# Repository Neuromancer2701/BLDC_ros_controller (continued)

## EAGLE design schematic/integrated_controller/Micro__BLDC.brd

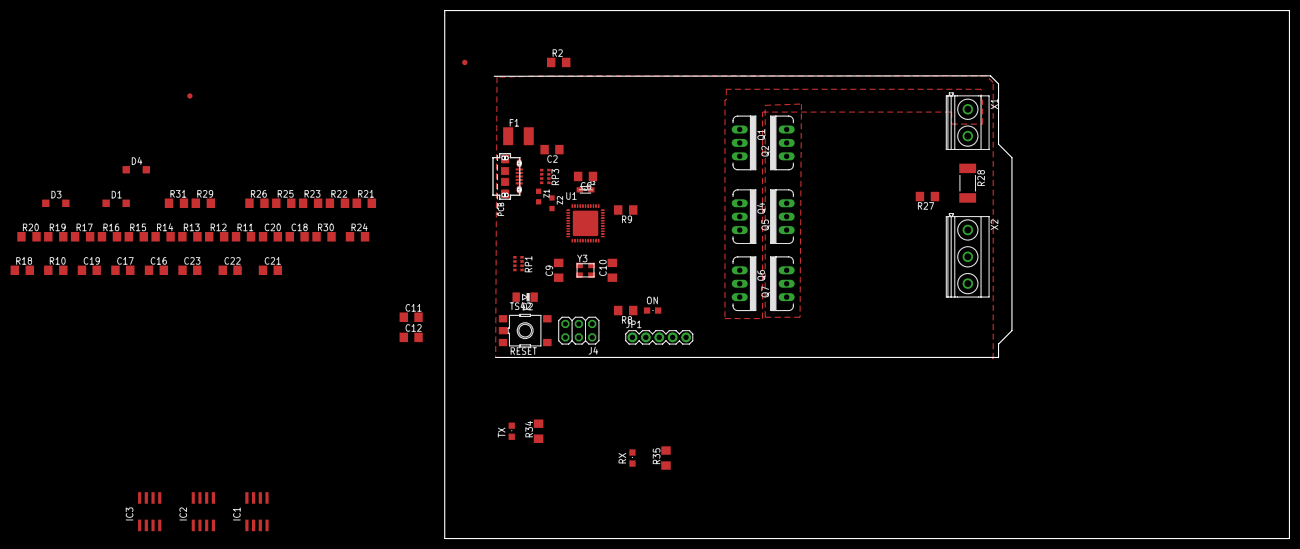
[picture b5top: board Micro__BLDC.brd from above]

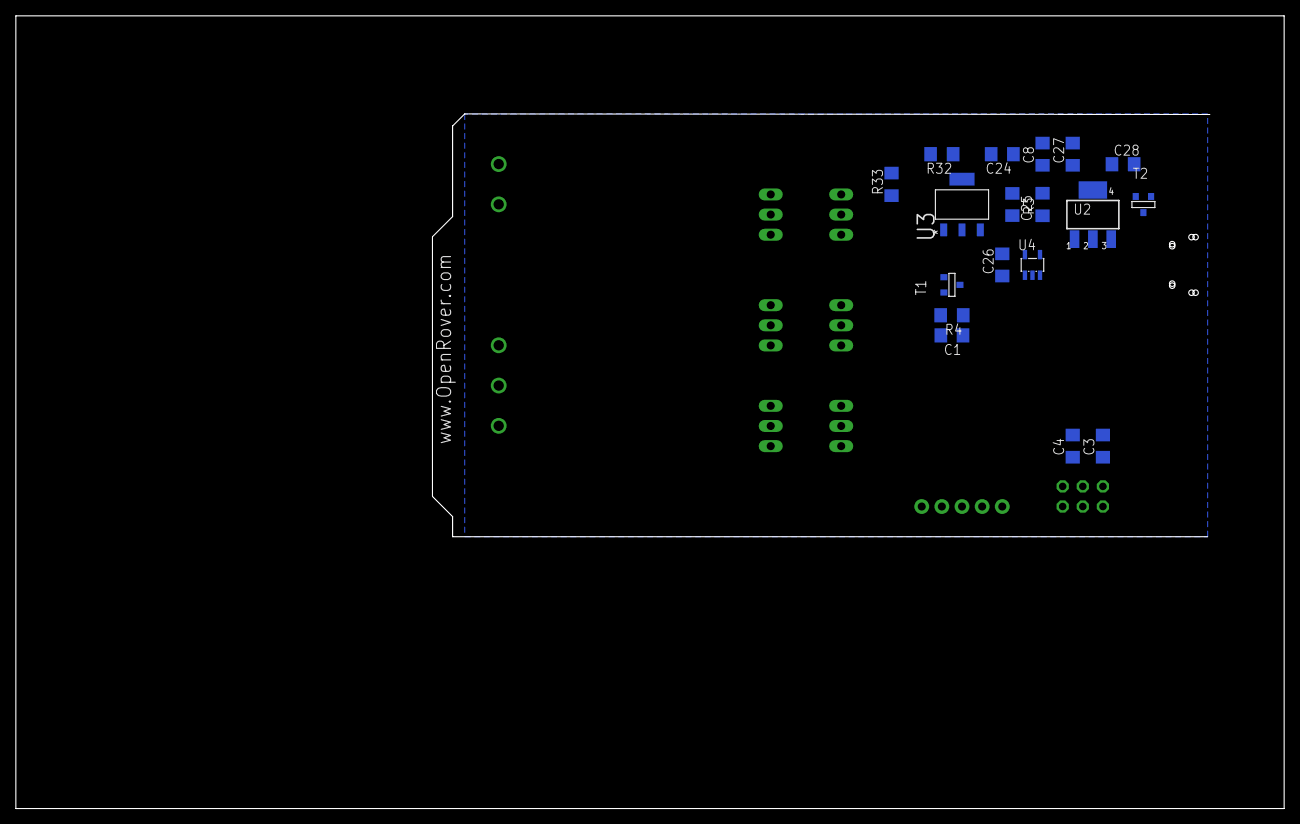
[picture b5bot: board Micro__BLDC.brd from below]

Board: 2 copper layers, 160.0 x 100.0 mm, 91 parts (18 on the bottom side), 67 nets, no tracks yet.

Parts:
C1, C3, C4, C8, C11, C28: 100n; C1206
C2, C27: 22u; C1206
C6, C12, C24: 1uF; C1206
C9, C10: 22pF; C1206
C16, C17, C19: 100nf; C1206
C18, C20: 22p; C1206
C21, C22, C23: 100pF; C1206
C25: 0.1u; C1206
C26: 1u; C1206
D1, D3, D4: MMSD914; SOD123
D2: CD1206-S01575; MINIMELF
F1: MF-MSMF050-2 500mA; L1812
IC1, IC2, IC3: IR2101SMD; SO08
J3: USB-MICRO!!!; CON2_USB_MICRO_B_AT
J4: 3x2M; 2X03
JP1: 1X05
L2: MH2029-300Y; 0805
ON: blue; CHIPLED_0805
Q1, Q2, Q4, Q5, Q6, Q7: TO220V
R2, R3, R4, R9: 10k; R1206
R8, R34, R35: 1k; R1206
R10: 200K; R1206
R11: 68k; R1206
R12, R13, R14, R15, R19, R22: 22; R1206
R16, R17, R21, R23, R26, R29: 22k; R1206
R18, R24, R30: 100k; R1206
R20, R25, R31: 15k; R1206
R27: 4.7k; R1206
R28: 0.001; R2512
R32: 240; R1206
R33: 2.2k; R1206
RESET: TS42
RP1, RP3: 22R; CAY16
RX: yellow; CHIPLED_0805
T1: FDN340P/PMV48XP; SOT-23
T2: PMV48XP; SOT-23
TX: yellow; CHIPLED_0805
U1: ATMEGA32U4-XUMU; QFN44ML7X7
U2: NCP1117-5; LINEAR_SOT223
U3: LM317DCY; SOT230P700X180-4N
U4: LP2985-33DBVR; SOT23-DBV
U$37: FIDUCIALMOUNT; FIDUCIA-MOUNT
U$53: FIDUCIAL1X2; FIDUCIAL-1X2
X1: MKDSN1,5/2-5,08
X2: MKDSN1,5/3-5,08
Y3: 16MHz KX-7; CRYSTAL-3.2-2.5
Z1, Z2: CG0603MLC-05E; CT/CN0603

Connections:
3V3: C26.2, U4.5
+5V: C3.1, C4.1, C8.2, C27.2, D2.C, J4.2, JP1.1, L2.1, R2.1, R8.2, T1.2, T2.3, U1.2, U1.14, U1.24, U1.34, U2.2, U2.4, U4.1, U4.3
+12V: C24.2, D1.A, D3.A, D4.A, IC1.1, IC2.1, IC3.1, R32.1, U3.2, U3.4
+VIN: C28.2, T2.2, U2.3
AREF: C11.1, U1.42
AVCC: C6.2, L2.2, U1.44
BLDC1: C16.1, C21.2, IC1.6, Q1.3, Q2.2, R16.2, R18.2, X2.1
BLDC2: C17.1, C22.2, IC2.6, Q4.3, Q5.2, R21.2, R24.2, X2.2
BLDC3: C19.1, C23.2, IC3.6, Q6.3, Q7.2, R26.2, R30.2, X2.3
CURRENT: Q2.3, Q5.3, Q7.3, R27.2, R28.2, U1.41
D+: J3.P3, RP3.8, Z1.1
D-: J3.P2, RP3.7, Z2.1
EMF1: R20.1, U1.39
EMF2: R25.1, U1.38
EMF3: R31.1, U1.37
GND: C1.2, C2.1, C3.2, C4.2, C6.1, C8.1, C9.1, C10.1, C11.2, C12.1, C18.1, C20.1, C21.1, C22.1, C23.1, C24.1, C25.1, C26.1, C27.1, C28.1, IC1.4, IC2.4, IC3.4, J3.P5, J3.S1, J3.S2, J3.S3, J3.S4, J3.S5, J3.S6, J4.6, JP1.5, ON.C, R3.2, R4.2, R9.1, R11.1, R17.1, R23.1, R28.1, R29.1, R33.2, RESET.3, RESET.4, RP1.3, RP1.4, RP1.5, RP1.6, RX.C, TX.C, U1.5, U1.15, U1.23, U1.35, U1.43, U1.EXP, U2.1, U4.2, X1.2, Y3.2, Y3.4, Z1.2, Z2.2
HALL1: JP1.2, U1.18
HALL2: JP1.3, U1.19
HALL3: JP1.4, U1.20
HI_1: IC1.2, U1.12
HI_2: IC2.2, U1.29
HI_3: IC3.2, U1.32
HWB: R9.2, U1.33
LOW_VOLTAGE: C20.2, R10.1, R11.2, U1.40
LO_1: IC1.3, U1.30
LO_2: IC2.3, U1.28
LO_3: IC3.3, U1.27
MISO: J4.1, U1.11
MOSI: J4.4, U1.10
unnamed: Q4.1, R15.1
unnamed: R35.1, RX.A
unnamed: ON.A, R8.1
unnamed: R34.1, TX.A
unnamed: R32.2, R33.1, U3.1
unnamed: C18.2, R27.1
unnamed: R16.1, R17.2
unnamed: R18.1, R20.2
unnamed: IC3.7, R19.2
unnamed: Q6.1, R19.1
unnamed: Q7.1, R22.1
unnamed: IC3.5, R22.2
unnamed: C19.2, D4.C, IC3.8
unnamed: R21.1, R23.2
unnamed: R24.1, R25.2
unnamed: IC2.7, R15.2
unnamed: Q5.1, R14.1
unnamed: IC2.5, R14.2
unnamed: C17.2, D3.C, IC2.8
unnamed: R26.1, R29.2
unnamed: R30.1, R31.2
unnamed: IC1.7, R13.2
unnamed: Q1.1, R13.1
unnamed: Q2.1, R12.1
unnamed: IC1.5, R12.2
unnamed: C16.2, D1.C, IC1.8
RD+: RP3.1, U1.4
RD-: RP3.2, U1.3
RESET: D2.A, J4.5, R2.2, RESET.2, U1.13
RXLED/SS: R35.2, U1.8
SCK: J4.3, U1.9
TXLED: R34.2, U1.22
UCAP: C12.2, U1.6
VCC: C25.2, Q1.2, Q4.2, Q6.2, R3.1, R10.2, T1.3, T2.1, U3.3, X1.1
VUSB: C1.1, F1.2, R4.1, T1.1, U1.7
VUSBD: C2.2, F1.1, J3.P1
XTAL1: C10.2, U1.17, Y3.3
XTAL2: C9.2, U1.16, Y3.1

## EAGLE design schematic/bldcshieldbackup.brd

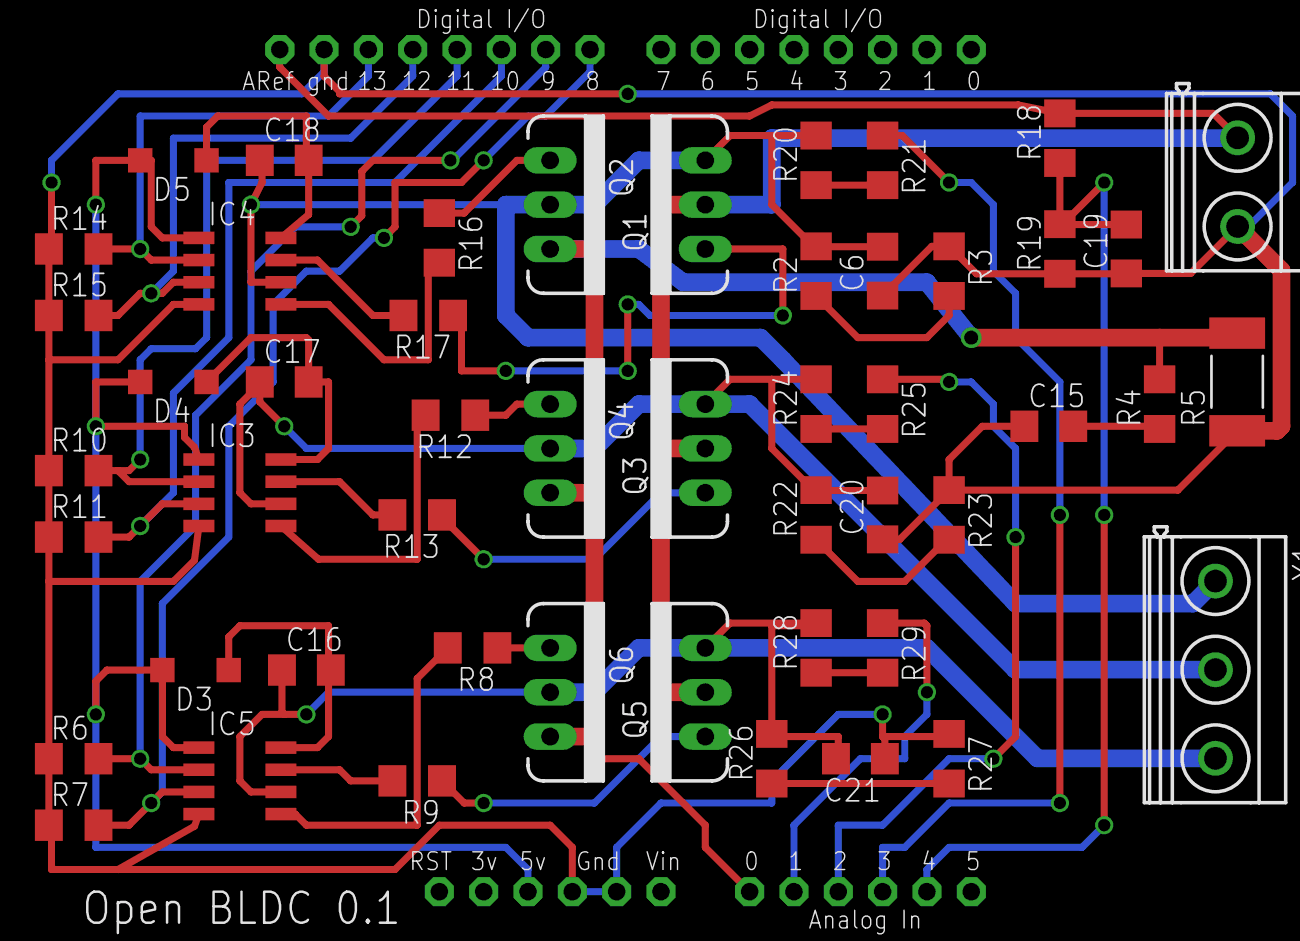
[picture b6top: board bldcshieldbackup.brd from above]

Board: 2 copper layers, 51 parts (0 on the bottom side), 36 nets.

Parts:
C6, C20, C21: 100pF; C1206
C15, C19: 22p; C1206
C16, C17, C18: 100nf; C1206
D3, D4, D5: MMSD914; SOD123
E$1: ARDUINO-NOHOLE
IC3, IC4, IC5: IR2101SMD; SO08
Q1, Q2, Q3, Q4, Q5, Q6: TO220V
R2, R3, R22, R23, R26, R27: 22k; R1206
R4: 4.7k; R1206
R5: 0.001; R2512
R6, R7, R10, R11, R14, R15: 10k; R1206
R8, R9, R12, R13, R16, R17: 22; R1206
R18: 200K; R1206
R19: 68k; R1206
R20, R24, R28: 100k; R1206
R21, R25, R29: 15k; R1206
X1: MKDSN1,5/3-5,08
X2: MKDSN1,5/2-5,08

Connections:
+5V: D3.A, D4.A, D5.A, IC3.1, IC4.1, IC5.1
BLDC1: C6.2, C18.1, IC4.6, Q1.3, Q2.2, R2.2, R20.2, X1.1
BLDC2: C17.1, C20.2, IC3.6, Q3.3, Q4.2, R22.2, R24.2, X1.2
BLDC3: C16.1, C21.2, IC5.6, Q5.3, Q6.2, R26.2, R28.2, X1.3
CURRENT: Q2.3, Q4.3, Q6.3
HI_1: E$1.D12, IC4.3, R15.2
HI_2: IC3.3, R11.2
HI_3: E$1.D8, IC5.3, R7.2
LOW_VOLTAGE: C19.2, R18.1, R19.2
LO_1: E$1.D13, IC4.2, R14.2
LO_3: IC5.2, R6.2
unnamed: Q3.1, R13.1
unnamed: R2.1, R3.2
unnamed: C15.2, R4.1
unnamed: R20.1, R21.2
unnamed: R22.1, R23.2
unnamed: IC5.7, R9.2
unnamed: Q5.1, R9.1
unnamed: Q6.1, R8.1
unnamed: IC5.5, R8.2
unnamed: C16.2, D3.C, IC5.8
unnamed: R24.1, R25.2
unnamed: IC3.7, R13.2
unnamed: Q4.1, R12.1
unnamed: IC3.5, R12.2
unnamed: C17.2, D4.C, IC3.8
unnamed: R26.1, R27.2
unnamed: R28.1, R29.2
unnamed: IC4.7, R17.2
unnamed: Q1.1, R17.1
unnamed: Q2.1, R16.1
unnamed: IC4.5, R16.2
unnamed: C18.2, D5.C, IC4.8
S$2: C21.1, IC3.4, IC4.4, IC5.4, R6.1, R7.1, R10.1, R11.1, R14.1, R15.1, R27.1
S$3: C6.1, C15.1, C19.1, C20.1, R3.1, R5.1, R19.1, R23.1, X2.2
VCC: Q1.2, Q3.2, Q5.2, R18.2, X2.1

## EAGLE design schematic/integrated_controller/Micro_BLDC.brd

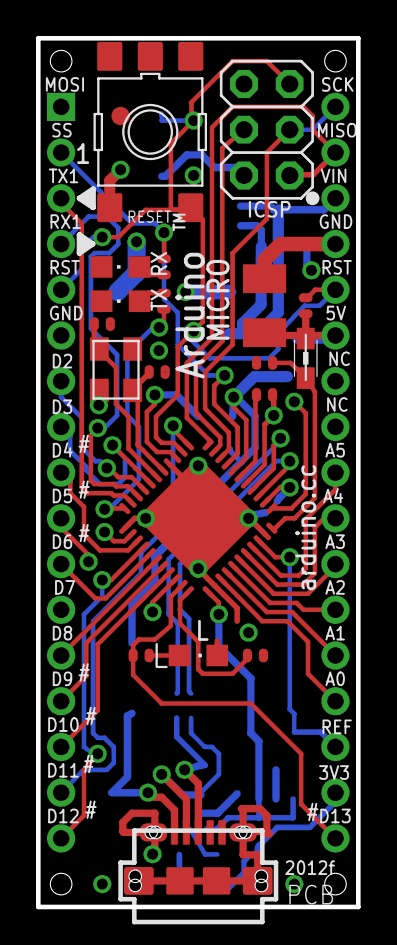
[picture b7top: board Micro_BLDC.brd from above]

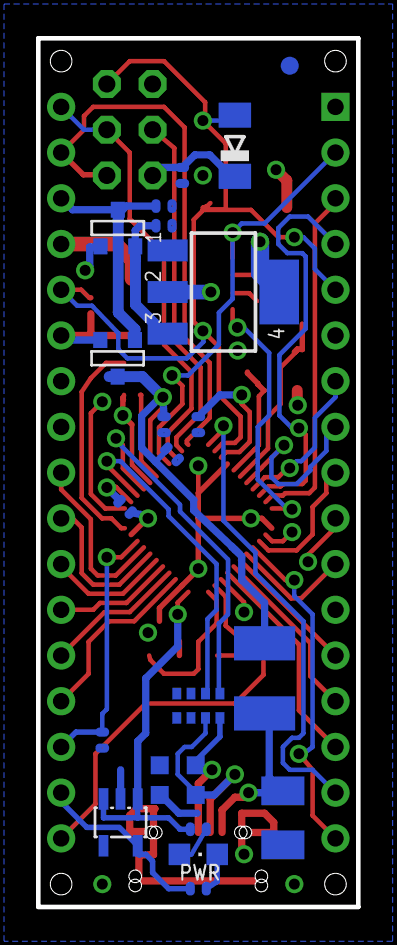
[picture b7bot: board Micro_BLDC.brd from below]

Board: 4 copper layers, 17.8 x 48.3 mm, 45 parts (22 on the bottom side), 47 nets.

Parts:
C1, C2, C6, C9, C10, C11: 100n; C0402
C3, C14: 22u; SMC_B
C4, C5, C7: 1uF; C0402
C12, C13: 22pF; C0402
D2: CD1206-S01575; MINIMELF
F1: MF-MSMF050-2 500mA; L1812
J3: USB-MICRO!!!; CON2_USB_MICRO_B_AT
J4: 3x2M; 2X03
J5: HEAD17-NOSS
J6: HEAD17-NOSS-1
L: green; CHIPLED_0805
L2: MH2029-300Y; 0805
ON: blue; CHIPLED_0805
R1, R2, R4, R9: 10K; R0402
R5, R6, R7, R8: 1K; R0402
RESET: TS42
RP3: 22R; CAY16
RX: yellow; CHIPLED_0805
T1: FDN340P/PMV48XP; SOT-23
T2: PMV48XP; SOT-23
TX: yellow; CHIPLED_0805
U1: ATMEGA32U4-XUMU; QFN44ML7X7
U2: NCP1117-5; SOT223
U4: LP2985-33DBVR; SOT23-DBV
U$3: DISCLAIMER
U$37: FIDUCIALMOUNT; FIDUCIA-MOUNT
U$53: FIDUCIAL1X2; FIDUCIAL-1X2
Y3: 16MHz KX-7; CRYSTAL-3.2-2.5
Z1, Z2: CG0603MLC-05E; CT/CN0603

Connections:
3V3: C4.1, J6.16, U4.5
+5V: C2.1, C3.+, C10.1, C11.1, D2.C, J4.2, J6.6, L2.1, R1.1, R5.1, T1.2, T2.3, U1.2, U1.14, U1.24, U1.34, U2.2, U2.4, U4.1, U4.3
+VIN: C1.1, T2.2, U2.3
A0: J6.14, U1.36
A1: J6.13, U1.37
A2: J6.12, U1.38
A3: J6.11, U1.39
A4: J6.10, U1.40
A5: J6.9, U1.41
AREF: C6.1, J6.15, U1.42
AVCC: C7.1, L2.2, U1.44
D0/RX: J5.4, U1.20
D1/TX: J5.3, U1.21
D2/SDA: J5.7, U1.19
D3/SCL: J5.8, U1.18
D4*: J5.9, U1.25
D5*: J5.10, U1.31
D6*: J5.11, U1.27
D7: J5.12, U1.1
D+: J3.P3, RP3.8, Z1.1
D-: J3.P2, RP3.7, Z2.1
GND: C1.2, C2.2, C3.-, C4.2, C5.2, C6.2, C7.2, C9.2, C10.2, C11.2, C12.1, C13.1, C14.-, J3.P5, J3.S1, J3.S2, J3.S3, J3.S4, J3.S5, J3.S6, J4.6, J5.6, J6.4, L.C, ON.C, R2.1, R4.2, R9.1, RESET.3, RESET.4, RP3.3, RP3.4, RP3.5, RP3.6, RX.C, TX.C, U1.5, U1.15, U1.23, U1.35, U1.43, U1.EXP, U2.1, U4.2, Y3.2, Y3.4, Z1.2, Z2.2
HWB: R4.1, U1.33
IO8: J5.13, U1.28
IO9*: J5.14, U1.29
IO10*: J5.15, U1.30
IO11*: J5.16, U1.12
IO12*: J5.17, U1.26
IO13*: J6.17, R8.1, U1.32
MISO: J4.1, J6.2, U1.11
MOSI: J4.4, J5.1, U1.10
unnamed: R7.2, RX.A
unnamed: ON.A, R5.2
unnamed: R6.2, TX.A
unnamed: L.A, R8.2
RD+: RP3.1, U1.4
RD-: RP3.2, U1.3
RESET: D2.A, J4.5, J5.5, J6.5, R1.2, RESET.2, U1.13
RXLED/SS: J5.2, R7.1, U1.8
SCK: J4.3, J6.1, U1.9
TXLED: R6.1, U1.22
UCAP: C5.1, U1.6
VIN: J6.3, R9.2, T1.3, T2.1
VUSB: C9.1, F1.2, R2.2, T1.1, U1.7
VUSBD: C14.+, F1.1, J3.P1
XTAL1: C13.2, U1.17, Y3.3
XTAL2: C12.2, U1.16, Y3.1

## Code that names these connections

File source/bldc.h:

// This file has been prepared for Doxygen automatic documentation generation.
//Seth M King

#ifndef __BLDC_H__
#define __BLDC_H__

#include <stdint.h>

enum commumationStates
{
    State1   = 0x04,
    State2   = 0x06,
    State3   = 0x02,
    State4   = 0x03,
    State5   = 0x01,
    State6   = 0x05
};

enum FET_PINS
{
    AH = 4,	 //! Port pin connected to phase A, high side enable switch. Arduino Pin 12
    AL = 12, //! Port pin connected to phase A, low side enable switch.  Arduino Pin 4

    BH = 9,	 //! Port pin connected to phase B, high side enable switch. Arduino Pin 9
    BL = 8,	 //! Port pin connected to phase B, low side enable switch. Arduino Pin 8

    CH = 5,	 //! Port pin connected to phase C, high side enable switch. Arduino Pin 5
    CL = 13	 //! Port pin connected to phase C, low side enable switch.	Arduino Pin 13
};

enum HALL_PINS
{
    HALL1 = 3,	 //! Port pin connected to phase A, high side enable switch. Arduino Pin 2
    HALL1_SHIFT = 2,
    HALL1_INDEX = 0,

    HALL2 = 6, //! Port pin connected to phase A, low side enable switch.  Arduino Pin 1
    HALL2_SHIFT = 1,
    HALL2_INDEX = 1,
    HALL3 = 7,	 //! Port pin connected to phase B, high side enable switch. Arduino Pin 0
    HALL3_INDEX = 2,
};



class BLDC
{
public:
	BLDC();
	virtual ~BLDC();

	void setSpeed(uint8_t _speed) {speed = _speed;}
	void Control();
	void CalculateCommutationState();

    commumationStates getCommunationState() { return currentCommunationState; }
    void setCurrentCommunationState(commumationStates CurrentCommunationState) {  currentCommunationState = CurrentCommunationState; }

    void setNewCommunationState(commumationStates NewCommunationState) { newCommunationState = NewCommunationState;
    }

    int* getRawHallData();

    char * stringData() {return &data[0];}

    void Reverse(){forward = false;}
    void Forward(){forward = true;}
    void ReadHalls();

    enum constants
    {
        NUMBER_HALLS = 3,
    };

private:
	unsigned char speed;
	bool forward;
    volatile int RawHallData[NUMBER_HALLS];
    commumationStates currentCommunationState;
    commumationStates newCommunationState;
    char data[256];
    int counter;




};



#endif 

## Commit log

2014-03-07 First commit added schematics and example code from atmel
2014-03-09 adding ros lib
2014-03-25 moved some files around and started on BLDC
2014-03-25 Changed the pin names removed some Iar headers
2014-04-06 changed file names and created a eclipse project. cleaned up naming and compiled as 328p
2014-04-06 added correct ISR for bottom
2014-04-15 making a class
2014-04-17 Changed extention to cpp and added ino test file
    moved to timer 2 so that timer 0 of arduino functions would not be
    altered. compiles for uno
2014-04-21 Update brd layout
2014-04-22 moved ino to arduino folder changed adc
    adc to match schematic
2014-04-22 Replace sparkfun part with adafruit
    drc is pretty good.
2014-04-23 Gerbers and some board changes
    Need to edit the shield part because the board is off when rendered.
2014-04-24 redoing brf layout from scatch
    deleted gerbers and backed up brd file
2014-04-25 Finished redoing the layout
    added board name and version as well as website. Built gerbers
2014-04-28 Finalized layout
    removed .7z changed to .zip submitted new boards with ground pours to
    dirty pcbs.
2014-05-20 Started working on motor profils
2014-05-29 added some helper functions
    for setting commutation state and getting adc values
2014-06-23 Changed some labels on the sch
    I think the finally routed pcb has never been committed.
2014-07-10 fixed a bug and commented out some code for testing
2014-07-11 working mega support
2014-10-08 jpeg of schematic added
2015-01-05 working on arduino micro version schematic
    also working on a hall effect code in the BLDC library
2015-02-24 pdfs for parts
2015-03-31 updated schematic
    updated schematic: removed pull down resistors and added 12V regulator
2015-04-05 Create LICENSE
2015-08-19 update protoytype
2015-12-17 add atmel studio project
2015-12-29 removed zip file
2016-01-04 started working on adc hall effect sensor code
2016-01-04 updated schematic and code
    added hall effect sensors
2016-01-05 continuing to work on pcb
2016-05-09 added wheel data
2016-05-16 added lookup tables for hall senses and created new functions
2016-05-17 got hall effects to commutation working with led fixture.
2016-06-16 changed commutation states and toasted the board.
2016-07-29 changed to d-paks on both sides of the board, working on traces. moved to eagle 7.6
2016-08-01 change fets to dpaks and changed the layout with multiple pours.
2016-08-18 created second folder for multiple piece board, rename files added some schematic from ST might be useful.
2016-08-19 working on layout of transistor board.
2016-08-21 finished with FET board generated gerbers.
2016-08-22 removing schematics of st board adding gerbers.
2016-08-22 started working on board one
2016-08-23 added lower line for upper transistor for all three half bridges to connector.
2016-08-24 stated working on main shield got connectors to FET boards done.
2017-04-22 created new shield version in schematic based off lessons from Chinese controller.
2017-05-23 refactoring bldc library.
2017-05-24 refactored bldc class and uploaded to cloud, compiles. now to test on hardware.
2017-05-25 troubleshot inputs fixed combitoral math.
2017-05-30 fixed missing trace.
2017-06-05 moved bldc files into dedicated folder. easier to link.
2017-06-08 continue working on code, FETs are turning on at the same time.
2017-06-08 moved files into lib folder
2017-06-08 changed all IO to direct IO removed softpwm. compile succesful
2017-06-08 got the motor spinning SOABgit statusgit status
2017-06-13 added support for reverse and test function. Forward and reverse works with PSU
2017-06-16 added new pwm library
2017-06-16 added a start motor sequence. started to added speed control and accelerating the motor. started to integrate the new pwm lib
2017-06-21 calculated velocity and working on pwm. problem with phase C high fet or io or wiring.
2017-06-22 added one publisher for the velocity and two subs for start and pwmduty cycle.
2017-06-22 added extra ros libs
2017-06-25 removed ROS because it was chew up too much ram, added serial protocol and PI pwm calculation based on speed.
2017-06-26 fixed and tested all serial commands. started implementing change of direction.
2017-06-28 added change of direction algorithm.
2017-07-24 fixed bug with refactoring working on second controller.
2017-12-20 working on new layout and swapped all transistors and wire pads. Need to look at better IO assignment and redo power supply.
2017-12-20 added lbr file for new part.
2017-12-25 added pdfs for new parts
2017-12-25 generated gerbers for new boards. might need some small tweaks on the keep out zones.
2017-12-26 tweaked lm507 board and made copy and created a board based on recon switcher.
2017-12-27 added pdfs and added LED fixture to the LM5007 board.
2018-04-12 added switcher pdf
